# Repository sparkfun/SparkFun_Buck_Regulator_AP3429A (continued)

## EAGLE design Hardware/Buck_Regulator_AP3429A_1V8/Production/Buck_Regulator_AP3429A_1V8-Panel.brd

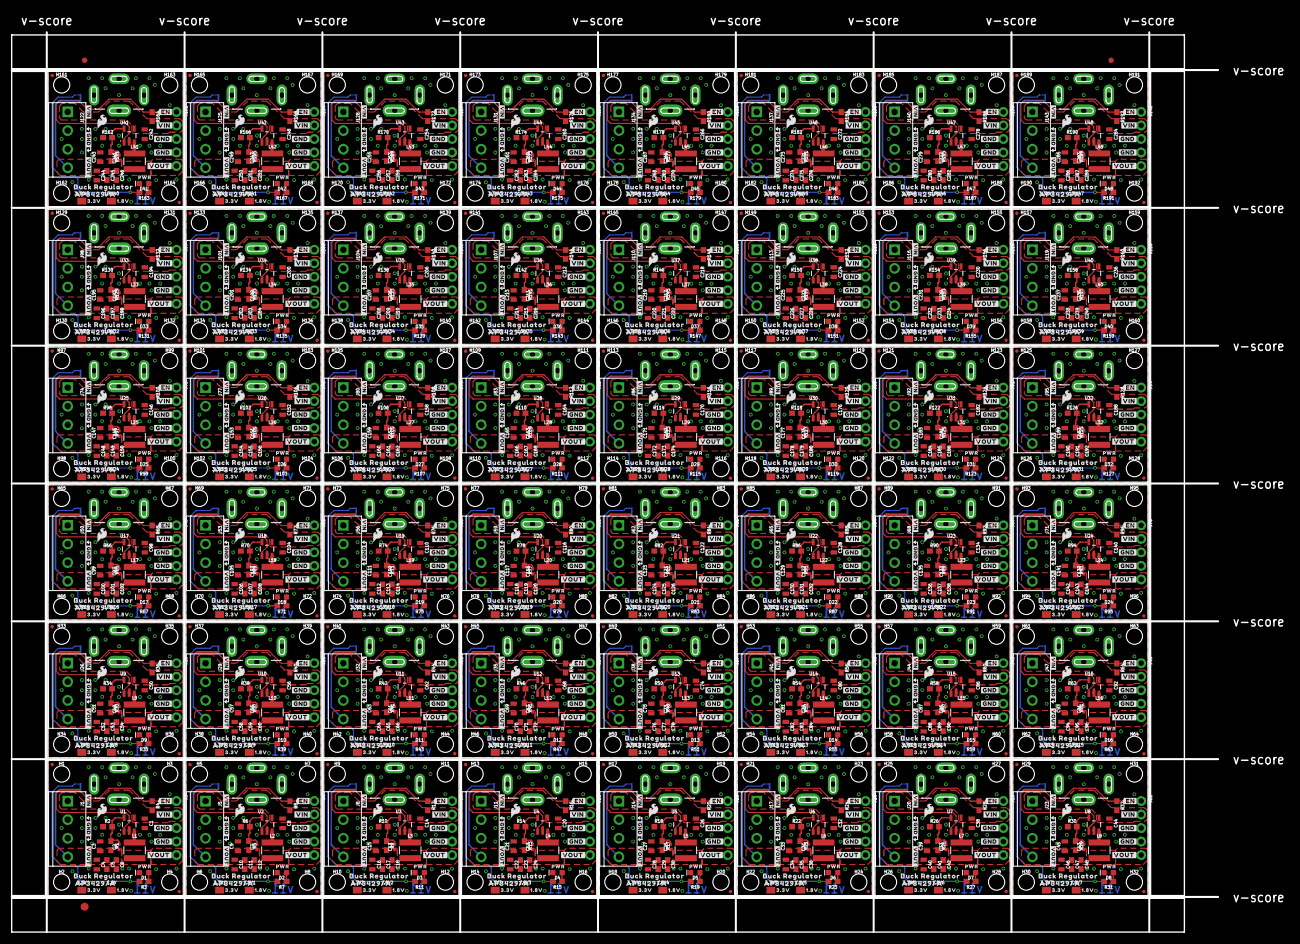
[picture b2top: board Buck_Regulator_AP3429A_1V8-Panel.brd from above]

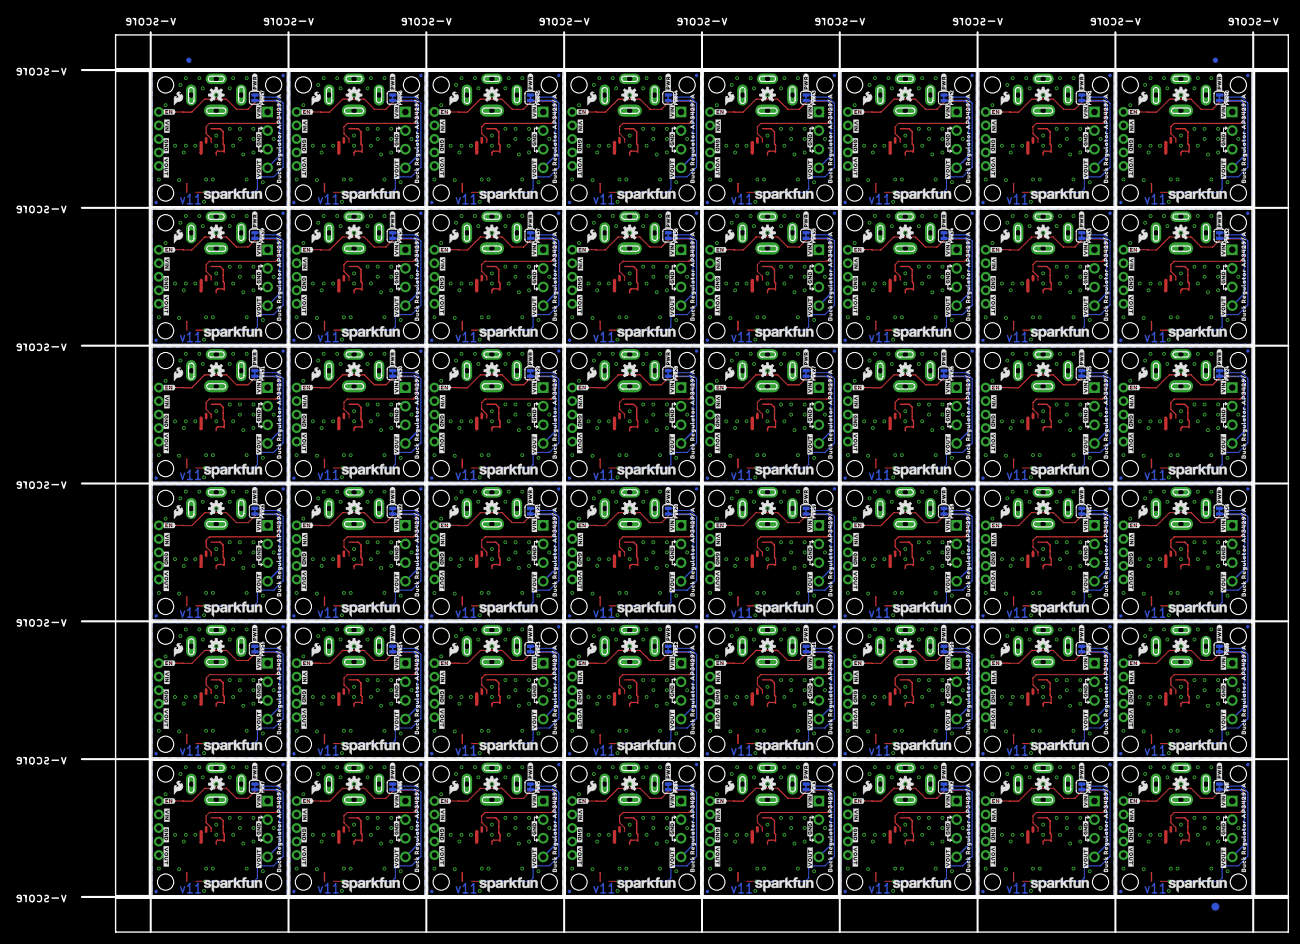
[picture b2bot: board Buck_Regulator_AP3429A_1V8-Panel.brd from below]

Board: 2 copper layers, 226.8 x 169.2 mm, 2550 parts (723 on the bottom side), 384 nets.

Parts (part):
1.8V, 1.8V1, 1.8V2, 1.8V3, 1.8V4, 1.8V5, 1.8V6, 1.8V7, 1.8V8, 1.8V9, 1.8V10, 1.8V11, 1.8V12, 1.8V13, 1.8V14, 1.8V15, 1.8V16, 1.8V17, 1.8V18, 1.8V19, 1.8V20, 1.8V21, 1.8V22, 1.8V23, 1.8V24, 1.8V25, 1.8V26, 1.8V27, 1.8V28, 1.8V29, 1.8V30, 1.8V31, 1.8V32, 1.8V33, 1.8V34, 1.8V35, 1.8V36, 1.8V37, 1.8V38, 1.8V39, 1.8V40, 1.8V41, 1.8V42, 1.8V43, 1.8V44, 1.8V45, 1.8V46, 1.8V47: PROD_ID_PASTE_NO-SILK; PRODUCT_IDENT_PASTE_NO-SILK
3.3V, 3.3V1, 3.3V2, 3.3V3, 3.3V4, 3.3V5, 3.3V6, 3.3V7, 3.3V8, 3.3V9, 3.3V10, 3.3V11, 3.3V12, 3.3V13, 3.3V14, 3.3V15, 3.3V16, 3.3V17, 3.3V18, 3.3V19, 3.3V20, 3.3V21, 3.3V22, 3.3V23, 3.3V24, 3.3V25, 3.3V26, 3.3V27, 3.3V28, 3.3V29, 3.3V30, 3.3V31, 3.3V32, 3.3V33, 3.3V34, 3.3V35, 3.3V36, 3.3V37, 3.3V38, 3.3V39, 3.3V40, 3.3V41, 3.3V42, 3.3V43, 3.3V44, 3.3V45, 3.3V46, 3.3V47: PROD_ID_NO-PASTE_NO_SILK; PRODUCT_IDENT_NO_NO-SILK
C1, C3, C4, C8, C9, C10, C14, C15, C16, C20, C21, C22, C26, C27, C28, C32, C33, C34, C38, C39, C40, C44, C45, C46, C50, C51, C52, C56, C57, C58, C62, C63, C64, C68, C69, C70, C74, C75, C76, C80, C81, C82, C86, C87, C88, C92, C93, C94, C98, C99, C100, C104, C105, C106, C110, C111, C112, C116, C117, C118, C122, C123, C124, C128, C129, C130, C134, C135, C136, C140, C141, C142, C146, C147, C148, C152, C153, C154, C158, C159, C160, C164, C165, C166, C170, C171, C172, C176, C177, C178, C182, C183, C184, C188, C189, C190, C194, C195, C196, C200, C201, C202, C206, C207, C208, C212, C213, C214, C218, C219, C220, C224, C225, C226, C230, C231, C232, C236, C237, C238, C242, C243, C244, C248, C249, C250, C254, C255, C256, C260, C261, C262, C266, C267, C268, C272, C273, C274, C278, C279, C280, C284, C285, C286: 22uF; 0805
C2, C7, C13, C19, C25, C31, C37, C43, C49, C55, C61, C67, C73, C79, C85, C91, C97, C103, C109, C115, C121, C127, C133, C139, C145, C151, C157, C163, C169, C175, C181, C187, C193, C199, C205, C211, C217, C223, C229, C235, C241, C247, C253, C259, C265, C271, C277, C283: 22pF; 0402-TIGHT
C5, C11, C17, C23, C29, C35, C41, C47, C53, C59, C65, C71, C77, C83, C89, C95, C101, C107, C113, C119, C125, C131, C137, C143, C149, C155, C161, C167, C173, C179, C185, C191, C197, C203, C209, C215, C221, C227, C233, C239, C245, C251, C257, C263, C269, C275, C281, C287: 0.1uF; 0603
C6, C12, C18, C24, C30, C36, C42, C48, C54, C60, C66, C72, C78, C84, C90, C96, C102, C108, C114, C120, C126, C132, C138, C144, C150, C156, C162, C168, C174, C180, C186, C192, C198, C204, C210, C216, C222, C228, C234, C240, C246, C252, C258, C264, C270, C276, C282, C288: 1.0uF; 0603
D1, D2, D3, D4, D5, D6, D7, D8, D9, D10, D11, D12, D13, D14, D15, D16, D17, D18, D19, D20, D21, D22, D23, D24, D25, D26, D27, D28, D29, D30, D31, D32, D33, D34, D35, D36, D37, D38, D39, D40, D41, D42, D43, D44, D45, D46, D47, D48: RED; LED-0603
E$1, E$2, E$3, E$4: FIDUCIAL-1X2
E$5, E$6: FIDUCIAL-1.5X3
FD1, FD2, FD3, FD4, FD5, FD6, FD7, FD8, FD9, FD10, FD11, FD12, FD13, FD14, FD15, FD16, FD17, FD18, FD19, FD20, FD21, FD22, FD23, FD24, FD25, FD26, FD27, FD28, FD29, FD30, FD31, FD32, FD33, FD34, FD35, FD36, FD37, FD38, FD39, FD40, FD41, FD42, FD43, FD44, FD45, FD46, FD47, FD48, FD49, FD50, FD51, FD52, FD53, FD54, FD55, FD56, FD57, FD58, FD59, FD60, FD61, FD62, FD63, FD64, FD65, FD66, FD67, FD68, FD69, FD70, FD71, FD72, FD73, FD74, FD75, FD76, FD77, FD78, FD79, FD80, FD81, FD82, FD83, FD84, FD85, FD86, FD87, FD88, FD89, FD90, FD91, FD92, FD93, FD94, FD95, FD96, FD97, FD98, FD99, FD100, FD101, FD102, FD103, FD104, FD105, FD106, FD107, FD108, FD109, FD110, FD111, FD112, FD113, FD114, FD115, FD116, FD117, FD118, FD119, FD120, FD121, FD122, FD123, FD124, FD125, FD126, FD127, FD128, FD129, FD130, FD131, FD132, FD133, FD134, FD135, FD136, FD137, FD138, FD139, FD140, FD141, FD142, FD143, FD144, FD145, FD146, FD147, FD148, FD149, FD150, FD151, FD152, FD153, FD154, FD155, FD156, FD157, FD158, FD159, FD160, FD161, FD162, FD163, FD164, FD165, FD166, FD167, FD168, FD169, FD170, FD171, FD172, FD173, FD174, FD175, FD176, FD177, FD178, FD179, FD180, FD181, FD182, FD183, FD184, FD185, FD186, FD187, FD188, FD189, FD190, FD191, FD192: FIDUCIALUFIDUCIAL; FIDUCIAL-MICRO
H1, H2, H3, H4, H5, H6, H7, H8, H9, H10, H11, H12, H13, H14, H15, H16, H17, H18, H19, H20, H21, H22, H23, H24, H25, H26, H27, H28, H29, H30, H31, H32, H33, H34, H35, H36, H37, H38, H39, H40, H41, H42, H43, H44, H45, H46, H47, H48, H49, H50, H51, H52, H53, H54, H55, H56, H57, H58, H59, H60, H61, H62, H63, H64, H65, H66, H67, H68, H69, H70, H71, H72, H73, H74, H75, H76, H77, H78, H79, H80, H81, H82, H83, H84, H85, H86, H87, H88, H89, H90, H91, H92, H93, H94, H95, H96, H97, H98, H99, H100, H101, H102, H103, H104, H105, H106, H107, H108, H109, H110, H111, H112, H113, H114, H115, H116, H117, H118, H119, H120, H121, H122, H123, H124, H125, H126, H127, H128, H129, H130, H131, H132, H133, H134, H135, H136, H137, H138, H139, H140, H141, H142, H143, H144, H145, H146, H147, H148, H149, H150, H151, H152, H153, H154, H155, H156, H157, H158, H159, H160, H161, H162, H163, H164, H165, H166, H167, H168, H169, H170, H171, H172, H173, H174, H175, H176, H177, H178, H179, H180, H181, H182, H183, H184, H185, H186, H187, H188, H189, H190, H191, H192: STAND-OFFTIGHT; STAND-OFF-TIGHT
J1, J5, J8, J11, J14, J17, J20, J23, J26, J29, J32, J35, J38, J41, J44, J47, J50, J53, J56, J59, J62, J65, J68, J71, J74, J77, J80, J83, J86, J89, J92, J95, J98, J101, J104, J107, J110, J113, J116, J119, J122, J125, J128, J131, J134, J137, J140, J143: Screw Terminal; SCREWTERMINAL-3.5MM-4
J2, J6, J9, J12, J15, J18, J21, J24, J27, J30, J33, J36, J39, J42, J45, J48, J51, J54, J57, J60, J63, J66, J69, J72, J75, J78, J81, J84, J87, J90, J93, J96, J99, J102, J105, J108, J111, J114, J117, J120, J123, J126, J129, J132, J135, J138, J141, J144: POWER_JACKPOWER_JACK_SLOT_COMBO; POWER_JACK_PTH_SLOT_BOTH
J3, J4, J7, J10, J13, J16, J19, J22, J25, J28, J31, J34, J37, J40, J43, J46, J49, J52, J55, J58, J61, J64, J67, J70, J73, J76, J79, J82, J85, J88, J91, J94, J97, J100, J103, J106, J109, J112, J115, J118, J121, J124, J127, J130, J133, J136, J139, J142: Breakout Headers; 1X05_NO_SILK
L1, L2, L3, L4, L5, L6, L7, L8, L9, L10, L11, L12, L13, L14, L15, L16, L17, L18, L19, L20, L21, L22, L23, L24, L25, L26, L27, L28, L29, L30, L31, L32, L33, L34, L35, L36, L37, L38, L39, L40, L41, L42, L43, L44, L45, L46, L47, L48: 2.2μH; INDUCTOR_4X4MM
LOGO1, LOGO4, LOGO7, LOGO10, LOGO13, LOGO16, LOGO19, LOGO22, LOGO25, LOGO28, LOGO31, LOGO34, LOGO37, LOGO40, LOGO43, LOGO46, LOGO49, LOGO52, LOGO55, LOGO58, LOGO61, LOGO64, LOGO67, LOGO70, LOGO73, LOGO76, LOGO79, LOGO82, LOGO85, LOGO88, LOGO91, LOGO94, LOGO97, LOGO100, LOGO103, LOGO106, LOGO109, LOGO112, LOGO115, LOGO118, LOGO121, LOGO124, LOGO127, LOGO130, LOGO133, LOGO136, LOGO139, LOGO142: OSHW-LOGOS; OSHW-LOGO-S
LOGO2, LOGO6, LOGO9, LOGO12, LOGO15, LOGO18, LOGO21, LOGO24, LOGO27, LOGO30, LOGO33, LOGO36, LOGO39, LOGO42, LOGO45, LOGO48, LOGO51, LOGO54, LOGO57, LOGO60, LOGO63, LOGO66, LOGO69, LOGO72, LOGO75, LOGO78, LOGO81, LOGO84, LOGO87, LOGO90, LOGO93, LOGO96, LOGO99, LOGO102, LOGO105, LOGO108, LOGO111, LOGO114, LOGO117, LOGO120, LOGO123, LOGO126, LOGO129, LOGO132, LOGO135, LOGO138, LOGO141, LOGO144: SFE_LOGO_NAME.1_INCH; SFE_LOGO_NAME_.1
LOGO3, LOGO5, LOGO8, LOGO11, LOGO14, LOGO17, LOGO20, LOGO23, LOGO26, LOGO29, LOGO32, LOGO35, LOGO38, LOGO41, LOGO44, LOGO47, LOGO50, LOGO53, LOGO56, LOGO59, LOGO62, LOGO65, LOGO68, LOGO71, LOGO74, LOGO77, LOGO80, LOGO83, LOGO86, LOGO89, LOGO92, LOGO95, LOGO98, LOGO101, LOGO104, LOGO107, LOGO110, LOGO113, LOGO116, LOGO119, LOGO122, LOGO125, LOGO128, LOGO131, LOGO134, LOGO137, LOGO140, LOGO143: SFE_LOGO_FLAME.1_INCH; SFE_LOGO_FLAME_.1
PWR, PWR1, PWR2, PWR3, PWR4, PWR5, PWR6, PWR7, PWR8, PWR9, PWR10, PWR11, PWR12, PWR13, PWR14, PWR15, PWR16, PWR17, PWR18, PWR19, PWR20, PWR21, PWR22, PWR23, PWR24, PWR25, PWR26, PWR27, PWR28, PWR29, PWR30, PWR31, PWR32, PWR33, PWR34, PWR35, PWR36, PWR37, PWR38, PWR39, PWR40, PWR41, PWR42, PWR43, PWR44, PWR45, PWR46, PWR47: JUMPER-SMT_2_NC_TRACE_SILK; SMT-JUMPER_2_NC_TRACE_SILK
R1, R5, R9, R13, R17, R21, R25, R29, R33, R37, R41, R45, R49, R53, R57, R61, R65, R69, R73, R77, R81, R85, R89, R93, R97, R101, R105, R109, R113, R117, R121, R125, R129, R133, R137, R141, R145, R149, R153, R157, R161, R165, R169, R173, R177, R181, R185, R189: 300k; 0603
R2, R6, R10, R14, R18, R22, R26, R30, R34, R38, R42, R46, R50, R54, R58, R62, R66, R70, R74, R78, R82, R86, R90, R94, R98, R102, R106, R110, R114, R118, R122, R126, R130, R134, R138, R142, R146, R150, R154, R158, R162, R166, R170, R174, R178, R182, R186, R190: 150k; 0603
R3, R7, R11, R15, R19, R23, R27, R31, R35, R39, R43, R47, R51, R55, R59, R63, R67, R71, R75, R79, R83, R87, R91, R95, R99, R103, R107, R111, R115, R119, R123, R127, R131, R135, R139, R143, R147, R151, R155, R159, R163, R167, R171, R175, R179, R183, R187, R191: 100; 0603
R4, R8, R12, R16, R20, R24, R28, R32, R36, R40, R44, R48, R52, R56, R60, R64, R68, R72, R76, R80, R84, R88, R92, R96, R100, R104, R108, R112, R116, R120, R124, R128, R132, R136, R140, R144, R148, R152, R156, R160, R164, R168, R172, R176, R180, R184, R188, R192: 100k; 0603
U1, U2, U3, U4, U5, U6, U7, U8, U9, U10, U11, U12, U13, U14, U15, U16, U17, U18, U19, U20, U21, U22, U23, U24, U25, U26, U27, U28, U29, U30, U31, U32, U33, U34, U35, U36, U37, U38, U39, U40, U41, U42, U43, U44, U45, U46, U47, U48: AP3429/A; SOT23-5
U$1, U$17, U$47, U$70, U$93, U$116, U$139, U$162, U$185, U$208, U$231, U$254, U$277, U$300, U$323, U$346, U$369, U$392, U$415, U$438, U$461, U$484, U$507, U$530, U$553, U$576, U$599, U$622, U$645, U$668, U$691, U$714, U$737, U$760, U$783, U$806, U$829, U$852, U$875, U$898, U$921, U$944, U$967, U$990, U$1013, U$1036, U$1059, U$1082: SFE_LOGO_FLAME_.1
U$2, U$18, U$48, U$71, U$94, U$117, U$140, U$163, U$186, U$209, U$232, U$255, U$278, U$301, U$324, U$347, U$370, U$393, U$416, U$439, U$462, U$485, U$508, U$531, U$554, U$577, U$600, U$623, U$646, U$669, U$692, U$715, U$738, U$761, U$784, U$807, U$830, U$853, U$876, U$899, U$922, U$945, U$968, U$991, U$1014, U$1037, U$1060, U$1083: BUCK_REGULATOR24
U$3, U$26, U$49, U$72, U$95, U$118, U$141, U$164, U$187, U$210, U$233, U$256, U$279, U$302, U$325, U$348, U$371, U$394, U$417, U$440, U$463, U$486, U$509, U$532, U$555, U$578, U$601, U$624, U$647, U$670, U$693, U$716, U$739, U$762, U$785, U$808, U$831, U$854, U$877, U$900, U$923, U$946, U$969, U$992, U$1015, U$1038, U$1061, U$1084: AP3429#A25
U$4, U$27, U$50, U$73, U$96, U$119, U$142, U$165, U$188, U$211, U$234, U$257, U$280, U$303, U$326, U$349, U$372, U$395, U$418, U$441, U$464, U$487, U$510, U$533, U$556, U$579, U$602, U$625, U$648, U$671, U$694, U$717, U$740, U$763, U$786, U$809, U$832, U$855, U$878, U$901, U$924, U$947, U$970, U$993, U$1016, U$1039, U$1062, U$1085: #VOUT#3431
U$5, U$6, U$28, U$29, U$51, U$52, U$74, U$75, U$97, U$98, U$120, U$121, U$143, U$144, U$166, U$167, U$189, U$190, U$212, U$213, U$235, U$236, U$258, U$259, U$281, U$282, U$304, U$305, U$327, U$328, U$350, U$351, U$373, U$374, U$396, U$397, U$419, U$420, U$442, U$443, U$465, U$466, U$488, U$489, U$511, U$512, U$534, U$535, U$557, U$558, U$580, U$581, U$603, U$604, U$626, U$627, U$649, U$650, U$672, U$673, U$695, U$696, U$718, U$719, U$741, U$742, U$764, U$765, U$787, U$788, U$810, U$811, U$833, U$834, U$856, U$857, U$879, U$880, U$902, U$903, U$925, U$926, U$948, U$949, U$971, U$972, U$994, U$995, U$1017, U$1018, U$1040, U$1041, U$1063, U$1064, U$1086, U$1087: #GND#3432
U$7, U$30, U$53, U$76, U$99, U$122, U$145, U$168, U$191, U$214, U$237, U$260, U$283, U$306, U$329, U$352, U$375, U$398, U$421, U$444, U$467, U$490, U$513, U$536, U$559, U$582, U$605, U$628, U$651, U$674, U$697, U$720, U$743, U$766, U$789, U$812, U$835, U$858, U$881, U$904, U$927, U$950, U$973, U$996, U$1019, U$1042, U$1065, U$1088: #VIN#3433
U$8, U$10, U$39, U$42, U$62, U$65, U$85, U$88, U$108, U$111, U$131, U$134, U$154, U$157, U$177, U$180, U$200, U$203, U$223, U$226, U$246, U$249, U$269, U$272, U$292, U$295, U$315, U$318, U$338, U$341, U$361, U$364, U$384, U$387, U$407, U$410, U$430, U$433, U$453, U$456, U$476, U$479, U$499, U$502, U$522, U$525, U$545, U$548, U$568, U$571, U$591, U$594, U$614, U$617, U$637, U$640, U$660, U$663, U$683, U$686, U$706, U$709, U$729, U$732, U$752, U$755, U$775, U$778, U$798, U$801, U$821, U$824, U$844, U$847, U$867, U$870, U$890, U$893, U$913, U$916, U$936, U$939, U$959, U$962, U$982, U$985, U$1005, U$1008, U$1028, U$1031, U$1051, U$1054, U$1074, U$1077, U$1097, U$1100: #GND#3446
U$9, U$15, U$38, U$44, U$61, U$67, U$84, U$90, U$107, U$113, U$130, U$136, U$153, U$159, U$176, U$182, U$199, U$205, U$222, U$228, U$245, U$251, U$268, U$274, U$291, U$297, U$314, U$320, U$337, U$343, U$360, U$366, U$383, U$389, U$406, U$412, U$429, U$435, U$452, U$458, U$475, U$481, U$498, U$504, U$521, U$527, U$544, U$550, U$567, U$573, U$590, U$596, U$613, U$619, U$636, U$642, U$659, U$665, U$682, U$688, U$705, U$711, U$728, U$734, U$751, U$757, U$774, U$780, U$797, U$803, U$820, U$826, U$843, U$849, U$866, U$872, U$889, U$895, U$912, U$918, U$935, U$941, U$958, U$964, U$981, U$987, U$1004, U$1010, U$1027, U$1033, U$1050, U$1056, U$1073, U$1079, U$1096, U$1102: #VIN#3445
U$11, U$13, U$40, U$43, U$63, U$66, U$86, U$89, U$109, U$112, U$132, U$135, U$155, U$158, U$178, U$181, U$201, U$204, U$224, U$227, U$247, U$250, U$270, U$273, U$293, U$296, U$316, U$319, U$339, U$342, U$362, U$365, U$385, U$388, U$408, U$411, U$431, U$434, U$454, U$457, U$477, U$480, U$500, U$503, U$523, U$526, U$546, U$549, U$569, U$572, U$592, U$595, U$615, U$618, U$638, U$641, U$661, U$664, U$684, U$687, U$707, U$710, U$730, U$733, U$753, U$756, U$776, U$779, U$799, U$802, U$822, U$825, U$845, U$848, U$868, U$871, U$891, U$894, U$914, U$917, U$937, U$940, U$960, U$963, U$983, U$986, U$1006, U$1009, U$1029, U$1032, U$1052, U$1055, U$1075, U$1078, U$1098, U$1101: #VOUT#3447
U$12, U$41, U$64, U$87, U$110, U$133, U$156, U$179, U$202, U$225, U$248, U$271, U$294, U$317, U$340, U$363, U$386, U$409, U$432, U$455, U$478, U$501, U$524, U$547, U$570, U$593, U$616, U$639, U$662, U$685, U$708, U$731, U$754, U$777, U$800, U$823, U$846, U$869, U$892, U$915, U$938, U$961, U$984, U$1007, U$1030, U$1053, U$1076, U$1099: #EN#3448
U$14, U$45, U$68, U$91, U$114, U$137, U$160, U$183, U$206, U$229, U$252, U$275, U$298, U$321, U$344, U$367, U$390, U$413, U$436, U$459, U$482, U$505, U$528, U$551, U$574, U$597, U$620, U$643, U$666, U$689, U$712, U$735, U$758, U$781, U$804, U$827, U$850, U$873, U$896, U$919, U$942, U$965, U$988, U$1011, U$1034, U$1057, U$1080, U$1103: #PWR#3451
U$16, U$46, U$69, U$92, U$115, U$138, U$161, U$184, U$207, U$230, U$253, U$276, U$299, U$322, U$345, U$368, U$391, U$414, U$437, U$460, U$483, U$506, U$529, U$552, U$575, U$598, U$621, U$644, U$667, U$690, U$713, U$736, U$759, U$782, U$805, U$828, U$851, U$874, U$897, U$920, U$943, U$966, U$989, U$1012, U$1035, U$1058, U$1081, U$1104: BUCK_REGULATOR_AP3429#A3453
U$19, U$35, U$58, U$81, U$104, U$127, U$150, U$173, U$196, U$219, U$242, U$265, U$288, U$311, U$334, U$357, U$380, U$403, U$426, U$449, U$472, U$495, U$518, U$541, U$564, U$587, U$610, U$633, U$656, U$679, U$702, U$725, U$748, U$771, U$794, U$817, U$840, U$863, U$886, U$909, U$932, U$955, U$978, U$1001, U$1024, U$1047, U$1070, U$1093: 1#8V3441
U$20, U$36, U$59, U$82, U$105, U$128, U$151, U$174, U$197, U$220, U$243, U$266, U$289, U$312, U$335, U$358, U$381, U$404, U$427, U$450, U$473, U$496, U$519, U$542, U$565, U$588, U$611, U$634, U$657, U$680, U$703, U$726, U$749, U$772, U$795, U$818, U$841, U$864, U$887, U$910, U$933, U$956, U$979, U$1002, U$1025, U$1048, U$1071, U$1094: PWR3441
U$21, U$31, U$54, U$77, U$100, U$123, U$146, U$169, U$192, U$215, U$238, U$261, U$284, U$307, U$330, U$353, U$376, U$399, U$422, U$445, U$468, U$491, U$514, U$537, U$560, U$583, U$606, U$629, U$652, U$675, U$698, U$721, U$744, U$767, U$790, U$813, U$836, U$859, U$882, U$905, U$928, U$951, U$974, U$997, U$1020, U$1043, U$1066, U$1089: #VOUT#3437
U$22, U$32, U$55, U$78, U$101, U$124, U$147, U$170, U$193, U$216, U$239, U$262, U$285, U$308, U$331, U$354, U$377, U$400, U$423, U$446, U$469, U$492, U$515, U$538, U$561, U$584, U$607, U$630, U$653, U$676, U$699, U$722, U$745, U$768, U$791, U$814, U$837, U$860, U$883, U$906, U$929, U$952, U$975, U$998, U$1021, U$1044, U$1067, U$1090: #VIN#3438
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
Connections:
EN: J3.1, R4.1, U1.1
EN1: J4.1, R8.1, U2.1
EN2: J7.1, R12.1, U3.1
EN3: J10.1, R16.1, U4.1
EN4: J13.1, R20.1, U5.1
EN5: J16.1, R24.1, U6.1
EN6: J19.1, R28.1, U7.1
EN7: J22.1, R32.1, U8.1
EN8: J25.1, R36.1, U9.1
EN9: J28.1, R40.1, U10.1
EN10: J31.1, R44.1, U11.1
EN11: J34.1, R48.1, U12.1
EN12: J37.1, R52.1, U13.1
EN13: J40.1, R56.1, U14.1
EN14: J43.1, R60.1, U15.1
EN15: J46.1, R64.1, U16.1
EN16: J49.1, R68.1, U17.1
EN17: J52.1, R72.1, U18.1
EN18: J55.1, R76.1, U19.1
EN19: J58.1, R80.1, U20.1
EN20: J61.1, R84.1, U21.1
EN21: J64.1, R88.1, U22.1
EN22: J67.1, R92.1, U23.1
EN23: J70.1, R96.1, U24.1
EN24: J73.1, R100.1, U25.1
EN25: J76.1, R104.1, U26.1
EN26: J79.1, R108.1, U27.1
EN27: J82.1, R112.1, U28.1
EN28: J85.1, R116.1, U29.1
EN29: J88.1, R120.1, U30.1
EN30: J91.1, R124.1, U31.1
EN31: J94.1, R128.1, U32.1
EN32: J97.1, R132.1, U33.1
EN33: J100.1, R136.1, U34.1
EN34: J103.1, R140.1, U35.1
EN35: J106.1, R144.1, U36.1
EN36: J109.1, R148.1, U37.1
EN37: J112.1, R152.1, U38.1
EN38: J115.1, R156.1, U39.1
EN39: J118.1, R160.1, U40.1
EN40: J121.1, R164.1, U41.1
EN41: J124.1, R168.1, U42.1
EN42: J127.1, R172.1, U43.1
EN43: J130.1, R176.1, U44.1
EN44: J133.1, R180.1, U45.1
EN45: J136.1, R184.1, U46.1
EN46: J139.1, R188.1, U47.1
EN47: J142.1, R192.1, U48.1
GND: C1.2, C3.2, C4.2, C5.2, C6.2, D1.C, J1.2, J1.3, J2.GND, J3.3, J3.4, R2.1, U1.2
GND1: C8.2, C9.2, C10.2, C11.2, C12.2, D2.C, J4.3, J4.4, J5.2, J5.3, J6.GND, R6.1, U2.2
GND2: C14.2, C15.2, C16.2, C17.2, C18.2, D3.C, J7.3, J7.4, J8.2, J8.3, J9.GND, R10.1, U3.2
GND3: C20.2, C21.2, C22.2, C23.2, C24.2, D4.C, J10.3, J10.4, J11.2, J11.3, J12.GND, R14.1, U4.2
GND4: C26.2, C27.2, C28.2, C29.2, C30.2, D5.C, J13.3, J13.4, J14.2, J14.3, J15.GND, R18.1, U5.2
GND5: C32.2, C33.2, C34.2, C35.2, C36.2, D6.C, J16.3, J16.4, J17.2, J17.3, J18.GND, R22.1, U6.2
GND6: C38.2, C39.2, C40.2, C41.2, C42.2, D7.C, J19.3, J19.4, J20.2, J20.3, J21.GND, R26.1, U7.2
GND7: C44.2, C45.2, C46.2, C47.2, C48.2, D8.C, J22.3, J22.4, J23.2, J23.3, J24.GND, R30.1, U8.2
GND8: C50.2, C51.2, C52.2, C53.2, C54.2, D9.C, J25.3, J25.4, J26.2, J26.3, J27.GND, R34.1, U9.2
GND9: C56.2, C57.2, C58.2, C59.2, C60.2, D10.C, J28.3, J28.4, J29.2, J29.3, J30.GND, R38.1, U10.2
GND10: C62.2, C63.2, C64.2, C65.2, C66.2, D11.C, J31.3, J31.4, J32.2, J32.3, J33.GND, R42.1, U11.2
GND11: C68.2, C69.2, C70.2, C71.2, C72.2, D12.C, J34.3, J34.4, J35.2, J35.3, J36.GND, R46.1, U12.2
GND12: C74.2, C75.2, C76.2, C77.2, C78.2, D13.C, J37.3, J37.4, J38.2, J38.3, J39.GND, R50.1, U13.2
GND13: C80.2, C81.2, C82.2, C83.2, C84.2, D14.C, J40.3, J40.4, J41.2, J41.3, J42.GND, R54.1, U14.2
GND14: C86.2, C87.2, C88.2, C89.2, C90.2, D15.C, J43.3, J43.4, J44.2, J44.3, J45.GND, R58.1, U15.2
GND15: C92.2, C93.2, C94.2, C95.2, C96.2, D16.C, J46.3, J46.4, J47.2, J47.3, J48.GND, R62.1, U16.2
GND16: C98.2, C99.2, C100.2, C101.2, C102.2, D17.C, J49.3, J49.4, J50.2, J50.3, J51.GND, R66.1, U17.2
GND17: C104.2, C105.2, C106.2, C107.2, C108.2, D18.C, J52.3, J52.4, J53.2, J53.3, J54.GND, R70.1, U18.2
GND18: C110.2, C111.2, C112.2, C113.2, C114.2, D19.C, J55.3, J55.4, J56.2, J56.3, J57.GND, R74.1, U19.2
GND19: C116.2, C117.2, C118.2, C119.2, C120.2, D20.C, J58.3, J58.4, J59.2, J59.3, J60.GND, R78.1, U20.2
GND20: C122.2, C123.2, C124.2, C125.2, C126.2, D21.C, J61.3, J61.4, J62.2, J62.3, J63.GND, R82.1, U21.2
GND21: C128.2, C129.2, C130.2, C131.2, C132.2, D22.C, J64.3, J64.4, J65.2, J65.3, J66.GND, R86.1, U22.2
GND22: C134.2, C135.2, C136.2, C137.2, C138.2, D23.C, J67.3, J67.4, J68.2, J68.3, J69.GND, R90.1, U23.2
GND23: C140.2, C141.2, C142.2, C143.2, C144.2, D24.C, J70.3, J70.4, J71.2, J71.3, J72.GND, R94.1, U24.2
GND24: C146.2, C147.2, C148.2, C149.2, C150.2, D25.C, J73.3, J73.4, J74.2, J74.3, J75.GND, R98.1, U25.2
GND25: C152.2, C153.2, C154.2, C155.2, C156.2, D26.C, J76.3, J76.4, J77.2, J77.3, J78.GND, R102.1, U26.2
GND26: C158.2, C159.2, C160.2, C161.2, C162.2, D27.C, J79.3, J79.4, J80.2, J80.3, J81.GND, R106.1, U27.2
GND27: C164.2, C165.2, C166.2, C167.2, C168.2, D28.C, J82.3, J82.4, J83.2, J83.3, J84.GND, R110.1, U28.2
GND28: C170.2, C171.2, C172.2, C173.2, C174.2, D29.C, J85.3, J85.4, J86.2, J86.3, J87.GND, R114.1, U29.2
GND29: C176.2, C177.2, C178.2, C179.2, C180.2, D30.C, J88.3, J88.4, J89.2, J89.3, J90.GND, R118.1, U30.2
GND30: C182.2, C183.2, C184.2, C185.2, C186.2, D31.C, J91.3, J91.4, J92.2, J92.3, J93.GND, R122.1, U31.2
GND31: C188.2, C189.2, C190.2, C191.2, C192.2, D32.C, J94.3, J94.4, J95.2, J95.3, J96.GND, R126.1, U32.2
GND32: C194.2, C195.2, C196.2, C197.2, C198.2, D33.C, J97.3, J97.4, J98.2, J98.3, J99.GND, R130.1, U33.2
GND33: C200.2, C201.2, C202.2, C203.2, C204.2, D34.C, J100.3, J100.4, J101.2, J101.3, J102.GND, R134.1, U34.2
GND34: C206.2, C207.2, C208.2, C209.2, C210.2, D35.C, J103.3, J103.4, J104.2, J104.3, J105.GND, R138.1, U35.2
GND35: C212.2, C213.2, C214.2, C215.2, C216.2, D36.C, J106.3, J106.4, J107.2, J107.3, J108.GND, R142.1, U36.2
GND36: C218.2, C219.2, C220.2, C221.2, C222.2, D37.C, J109.3, J109.4, J110.2, J110.3, J111.GND, R146.1, U37.2
GND37: C224.2, C225.2, C226.2, C227.2, C228.2, D38.C, J112.3, J112.4, J113.2, J113.3, J114.GND, R150.1, U38.2
GND38: C230.2, C231.2, C232.2, C233.2, C234.2, D39.C, J115.3, J115.4, J116.2, J116.3, J117.GND, R154.1, U39.2
GND39: C236.2, C237.2, C238.2, C239.2, C240.2, D40.C, J118.3, J118.4, J119.2, J119.3, J120.GND, R158.1, U40.2
GND40: C242.2, C243.2, C244.2, C245.2, C246.2, D41.C, J121.3, J121.4, J122.2, J122.3, J123.GND, R162.1, U41.2
GND41: C248.2, C249.2, C250.2, C251.2, C252.2, D42.C, J124.3, J124.4, J125.2, J125.3, J126.GND, R166.1, U42.2
GND42: C254.2, C255.2, C256.2, C257.2, C258.2, D43.C, J127.3, J127.4, J128.2, J128.3, J129.GND, R170.1, U43.2
GND43: C260.2, C261.2, C262.2, C263.2, C264.2, D44.C, J130.3, J130.4, J131.2, J131.3, J132.GND, R174.1, U44.2
GND44: C266.2, C267.2, C268.2, C269.2, C270.2, D45.C, J133.3, J133.4, J134.2, J134.3, J135.GND, R178.1, U45.2
GND45: C272.2, C273.2, C274.2, C275.2, C276.2, D46.C, J136.3, J136.4, J137.2, J137.3, J138.GND, R182.1, U46.2
GND46: C278.2, C279.2, C280.2, C281.2, C282.2, D47.C, J139.3, J139.4, J140.2, J140.3, J141.GND, R186.1, U47.2
GND47: C284.2, C285.2, C286.2, C287.2, C288.2, D48.C, J142.3, J142.4, J143.2, J143.3, J144.GND, R190.1, U48.2
unnamed: L1.P$1, U1.3
unnamed: C2.2, R1.1, R2.2, U1.5
unnamed: PWR.1, R3.2
unnamed: D1.A, R3.1
unnamed: L2.P$1, U2.3
unnamed: C7.2, R5.1, R6.2, U2.5
unnamed: PWR1.1, R7.2
unnamed: D2.A, R7.1
unnamed: L3.P$1, U3.3
unnamed: C13.2, R9.1, R10.2, U3.5
unnamed: PWR2.1, R11.2
unnamed: D3.A, R11.1
unnamed: L4.P$1, U4.3
unnamed: C19.2, R13.1, R14.2, U4.5
unnamed: PWR3.1, R15.2
unnamed: D4.A, R15.1
unnamed: L5.P$1, U5.3
unnamed: C25.2, R17.1, R18.2, U5.5
unnamed: PWR4.1, R19.2
unnamed: D5.A, R19.1
unnamed: L6.P$1, U6.3
unnamed: C31.2, R21.1, R22.2, U6.5
unnamed: PWR5.1, R23.2
unnamed: D6.A, R23.1
unnamed: L7.P$1, U7.3
unnamed: C37.2, R25.1, R26.2, U7.5
unnamed: PWR6.1, R27.2
unnamed: D7.A, R27.1
unnamed: L8.P$1, U8.3
unnamed: C43.2, R29.1, R30.2, U8.5
unnamed: PWR7.1, R31.2
unnamed: D8.A, R31.1
unnamed: L9.P$1, U9.3
unnamed: C49.2, R33.1, R34.2, U9.5
unnamed: PWR8.1, R35.2
unnamed: D9.A, R35.1
unnamed: L10.P$1, U10.3
unnamed: C55.2, R37.1, R38.2, U10.5
unnamed: PWR9.1, R39.2
unnamed: D10.A, R39.1
unnamed: L11.P$1, U11.3
unnamed: C61.2, R41.1, R42.2, U11.5
unnamed: PWR10.1, R43.2
unnamed: D11.A, R43.1
unnamed: L12.P$1, U12.3
unnamed: C67.2, R45.1, R46.2, U12.5
unnamed: PWR11.1, R47.2
unnamed: D12.A, R47.1
unnamed: L13.P$1, U13.3
unnamed: C73.2, R49.1, R50.2, U13.5
unnamed: PWR12.1, R51.2
unnamed: D13.A, R51.1
unnamed: L14.P$1, U14.3
unnamed: C79.2, R53.1, R54.2, U14.5
unnamed: PWR13.1, R55.2
unnamed: D14.A, R55.1
unnamed: L15.P$1, U15.3
unnamed: C85.2, R57.1, R58.2, U15.5
unnamed: PWR14.1, R59.2
unnamed: D15.A, R59.1
unnamed: L16.P$1, U16.3
unnamed: C91.2, R61.1, R62.2, U16.5
unnamed: PWR15.1, R63.2
unnamed: D16.A, R63.1
unnamed: L17.P$1, U17.3
unnamed: C97.2, R65.1, R66.2, U17.5
unnamed: PWR16.1, R67.2
unnamed: D17.A, R67.1
unnamed: L18.P$1, U18.3
unnamed: C103.2, R69.1, R70.2, U18.5
unnamed: PWR17.1, R71.2
unnamed: D18.A, R71.1
unnamed: L19.P$1, U19.3
unnamed: C109.2, R73.1, R74.2, U19.5
unnamed: PWR18.1, R75.2
unnamed: D19.A, R75.1
unnamed: L20.P$1, U20.3
unnamed: C115.2, R77.1, R78.2, U20.5
unnamed: PWR19.1, R79.2
unnamed: D20.A, R79.1
unnamed: L21.P$1, U21.3
unnamed: C121.2, R81.1, R82.2, U21.5
unnamed: PWR20.1, R83.2
unnamed: D21.A, R83.1
unnamed: L22.P$1, U22.3
unnamed: C127.2, R85.1, R86.2, U22.5
unnamed: PWR21.1, R87.2
unnamed: D22.A, R87.1
unnamed: L23.P$1, U23.3
unnamed: C133.2, R89.1, R90.2, U23.5
unnamed: PWR22.1, R91.2
unnamed: D23.A, R91.1
unnamed: L24.P$1, U24.3
unnamed: C139.2, R93.1, R94.2, U24.5
unnamed: PWR23.1, R95.2
unnamed: D24.A, R95.1
unnamed: L25.P$1, U25.3
unnamed: C145.2, R97.1, R98.2, U25.5
unnamed: PWR24.1, R99.2
unnamed: D25.A, R99.1
unnamed: L26.P$1, U26.3
unnamed: C151.2, R101.1, R102.2, U26.5
unnamed: PWR25.1, R103.2
unnamed: D26.A, R103.1
unnamed: L27.P$1, U27.3
unnamed: C157.2, R105.1, R106.2, U27.5
unnamed: PWR26.1, R107.2
unnamed: D27.A, R107.1
unnamed: L28.P$1, U28.3
unnamed: C163.2, R109.1, R110.2, U28.5
unnamed: PWR27.1, R111.2
unnamed: D28.A, R111.1
unnamed: L29.P$1, U29.3
unnamed: C169.2, R113.1, R114.2, U29.5
unnamed: PWR28.1, R115.2
unnamed: D29.A, R115.1
unnamed: L30.P$1, U30.3
unnamed: C175.2, R117.1, R118.2, U30.5
unnamed: PWR29.1, R119.2
unnamed: D30.A, R119.1
unnamed: L31.P$1, U31.3
unnamed: C181.2, R121.1, R122.2, U31.5
unnamed: PWR30.1, R123.2
unnamed: D31.A, R123.1
unnamed: L32.P$1, U32.3
unnamed: C187.2, R125.1, R126.2, U32.5
unnamed: PWR31.1, R127.2
unnamed: D32.A, R127.1
unnamed: L33.P$1, U33.3
unnamed: C193.2, R129.1, R130.2, U33.5
unnamed: PWR32.1, R131.2
unnamed: D33.A, R131.1
unnamed: L34.P$1, U34.3
unnamed: C199.2, R133.1, R134.2, U34.5
unnamed: PWR33.1, R135.2
unnamed: D34.A, R135.1
unnamed: L35.P$1, U35.3
unnamed: C205.2, R137.1, R138.2, U35.5
unnamed: PWR34.1, R139.2
unnamed: D35.A, R139.1
unnamed: L36.P$1, U36.3
unnamed: C211.2, R141.1, R142.2, U36.5
unnamed: PWR35.1, R143.2
unnamed: D36.A, R143.1
unnamed: L37.P$1, U37.3
unnamed: C217.2, R145.1, R146.2, U37.5
unnamed: PWR36.1, R147.2
unnamed: D37.A, R147.1
unnamed: L38.P$1, U38.3
unnamed: C223.2, R149.1, R150.2, U38.5
unnamed: PWR37.1, R151.2
unnamed: D38.A, R151.1
unnamed: L39.P$1, U39.3
unnamed: C229.2, R153.1, R154.2, U39.5
unnamed: PWR38.1, R155.2
unnamed: D39.A, R155.1
unnamed: L40.P$1, U40.3
unnamed: C235.2, R157.1, R158.2, U40.5
unnamed: PWR39.1, R159.2
unnamed: D40.A, R159.1
unnamed: L41.P$1, U41.3
unnamed: C241.2, R161.1, R162.2, U41.5
unnamed: PWR40.1, R163.2
unnamed: D41.A, R163.1
unnamed: L42.P$1, U42.3
unnamed: C247.2, R165.1, R166.2, U42.5
unnamed: PWR41.1, R167.2
unnamed: D42.A, R167.1
unnamed: L43.P$1, U43.3
unnamed: C253.2, R169.1, R170.2, U43.5
unnamed: PWR42.1, R171.2
unnamed: D43.A, R171.1
unnamed: L44.P$1, U44.3
unnamed: C259.2, R173.1, R174.2, U44.5
unnamed: PWR43.1, R175.2
unnamed: D44.A, R175.1
unnamed: L45.P$1, U45.3
unnamed: C265.2, R177.1, R178.2, U45.5
unnamed: PWR44.1, R179.2
unnamed: D45.A, R179.1
unnamed: L46.P$1, U46.3
unnamed: C271.2, R181.1, R182.2, U46.5
unnamed: PWR45.1, R183.2
unnamed: D46.A, R183.1
unnamed: L47.P$1, U47.3
unnamed: C277.2, R185.1, R186.2, U47.5
unnamed: PWR46.1, R187.2
unnamed: D47.A, R187.1
unnamed: L48.P$1, U48.3
unnamed: C283.2, R189.1, R190.2, U48.5
unnamed: PWR47.1, R191.2
unnamed: D48.A, R191.1
VIN: C1.1, J1.1, J2.PWR, J3.2, R4.2, U1.4
VIN1: C8.1, J4.2, J5.1, J6.PWR, R8.2, U2.4
VIN2: C14.1, J7.2, J8.1, J9.PWR, R12.2, U3.4
VIN3: C20.1, J10.2, J11.1, J12.PWR, R16.2, U4.4
VIN4: C26.1, J13.2, J14.1, J15.PWR, R20.2, U5.4
VIN5: C32.1, J16.2, J17.1, J18.PWR, R24.2, U6.4
VIN6: C38.1, J19.2, J20.1, J21.PWR, R28.2, U7.4
VIN7: C44.1, J22.2, J23.1, J24.PWR, R32.2, U8.4
VIN8: C50.1, J25.2, J26.1, J27.PWR, R36.2, U9.4
VIN9: C56.1, J28.2, J29.1, J30.PWR, R40.2, U10.4
VIN10: C62.1, J31.2, J32.1, J33.PWR, R44.2, U11.4
VIN11: C68.1, J34.2, J35.1, J36.PWR, R48.2, U12.4
VIN12: C74.1, J37.2, J38.1, J39.PWR, R52.2, U13.4
VIN13: C80.1, J40.2, J41.1, J42.PWR, R56.2, U14.4
VIN14: C86.1, J43.2, J44.1, J45.PWR, R60.2, U15.4
VIN15: C92.1, J46.2, J47.1, J48.PWR, R64.2, U16.4
VIN16: C98.1, J49.2, J50.1, J51.PWR, R68.2, U17.4
VIN17: C104.1, J52.2, J53.1, J54.PWR, R72.2, U18.4
VIN18: C110.1, J55.2, J56.1, J57.PWR, R76.2, U19.4
VIN19: C116.1, J58.2, J59.1, J60.PWR, R80.2, U20.4
VIN20: C122.1, J61.2, J62.1, J63.PWR, R84.2, U21.4
VIN21: C128.1, J64.2, J65.1, J66.PWR, R88.2, U22.4
VIN22: C134.1, J67.2, J68.1, J69.PWR, R92.2, U23.4
VIN23: C140.1, J70.2, J71.1, J72.PWR, R96.2, U24.4
VIN24: C146.1, J73.2, J74.1, J75.PWR, R100.2, U25.4
VIN25: C152.1, J76.2, J77.1, J78.PWR, R104.2, U26.4
VIN26: C158.1, J79.2, J80.1, J81.PWR, R108.2, U27.4
VIN27: C164.1, J82.2, J83.1, J84.PWR, R112.2, U28.4
VIN28: C170.1, J85.2, J86.1, J87.PWR, R116.2, U29.4
VIN29: C176.1, J88.2, J89.1, J90.PWR, R120.2, U30.4
VIN30: C182.1, J91.2, J92.1, J93.PWR, R124.2, U31.4
VIN31: C188.1, J94.2, J95.1, J96.PWR, R128.2, U32.4
VIN32: C194.1, J97.2, J98.1, J99.PWR, R132.2, U33.4
VIN33: C200.1, J100.2, J101.1, J102.PWR, R136.2, U34.4
VIN34: C206.1, J103.2, J104.1, J105.PWR, R140.2, U35.4
VIN35: C212.1, J106.2, J107.1, J108.PWR, R144.2, U36.4
VIN36: C218.1, J109.2, J110.1, J111.PWR, R148.2, U37.4
VIN37: C224.1, J112.2, J113.1, J114.PWR, R152.2, U38.4
VIN38: C230.1, J115.2, J116.1, J117.PWR, R156.2, U39.4
VIN39: C236.1, J118.2, J119.1, J120.PWR, R160.2, U40.4
VIN40: C242.1, J121.2, J122.1, J123.PWR, R164.2, U41.4
VIN41: C248.1, J124.2, J125.1, J126.PWR, R168.2, U42.4
VIN42: C254.1, J127.2, J128.1, J129.PWR, R172.2, U43.4
VIN43: C260.1, J130.2, J131.1, J132.PWR, R176.2, U44.4
VIN44: C266.1, J133.2, J134.1, J135.PWR, R180.2, U45.4
VIN45: C272.1, J136.2, J137.1, J138.PWR, R184.2, U46.4
VIN46: C278.1, J139.2, J140.1, J141.PWR, R188.2, U47.4
VIN47: C284.1, J142.2, J143.1, J144.PWR, R192.2, U48.4
VOUT: C2.1, C3.1, C4.1, C5.1, C6.1, J1.4, J3.5, L1.P$2, PWR.2, R1.2
VOUT1: C7.1, C9.1, C10.1, C11.1, C12.1, J4.5, J5.4, L2.P$2, PWR1.2, R5.2
VOUT2: C13.1, C15.1, C16.1, C17.1, C18.1, J7.5, J8.4, L3.P$2, PWR2.2, R9.2
VOUT3: C19.1, C21.1, C22.1, C23.1, C24.1, J10.5, J11.4, L4.P$2, PWR3.2, R13.2
VOUT4: C25.1, C27.1, C28.1, C29.1, C30.1, J13.5, J14.4, L5.P$2, PWR4.2, R17.2
VOUT5: C31.1, C33.1, C34.1, C35.1, C36.1, J16.5, J17.4, L6.P$2, PWR5.2, R21.2
VOUT6: C37.1, C39.1, C40.1, C41.1, C42.1, J19.5, J20.4, L7.P$2, PWR6.2, R25.2
VOUT7: C43.1, C45.1, C46.1, C47.1, C48.1, J22.5, J23.4, L8.P$2, PWR7.2, R29.2
VOUT8: C49.1, C51.1, C52.1, C53.1, C54.1, J25.5, J26.4, L9.P$2, PWR8.2, R33.2
VOUT9: C55.1, C57.1, C58.1, C59.1, C60.1, J28.5, J29.4, L10.P$2, PWR9.2, R37.2
VOUT10: C61.1, C63.1, C64.1, C65.1, C66.1, J31.5, J32.4, L11.P$2, PWR10.2, R41.2
VOUT11: C67.1, C69.1, C70.1, C71.1, C72.1, J34.5, J35.4, L12.P$2, PWR11.2, R45.2
VOUT12: C73.1, C75.1, C76.1, C77.1, C78.1, J37.5, J38.4, L13.P$2, PWR12.2, R49.2
VOUT13: C79.1, C81.1, C82.1, C83.1, C84.1, J40.5, J41.4, L14.P$2, PWR13.2, R53.2
VOUT14: C85.1, C87.1, C88.1, C89.1, C90.1, J43.5, J44.4, L15.P$2, PWR14.2, R57.2
VOUT15: C91.1, C93.1, C94.1, C95.1, C96.1, J46.5, J47.4, L16.P$2, PWR15.2, R61.2
VOUT16: C97.1, C99.1, C100.1, C101.1, C102.1, J49.5, J50.4, L17.P$2, PWR16.2, R65.2
VOUT17: C103.1, C105.1, C106.1, C107.1, C108.1, J52.5, J53.4, L18.P$2, PWR17.2, R69.2
VOUT18: C109.1, C111.1, C112.1, C113.1, C114.1, J55.5, J56.4, L19.P$2, PWR18.2, R73.2
VOUT19: C115.1, C117.1, C118.1, C119.1, C120.1, J58.5, J59.4, L20.P$2, PWR19.2, R77.2
VOUT20: C121.1, C123.1, C124.1, C125.1, C126.1, J61.5, J62.4, L21.P$2, PWR20.2, R81.2
VOUT21: C127.1, C129.1, C130.1, C131.1, C132.1, J64.5, J65.4, L22.P$2, PWR21.2, R85.2
VOUT22: C133.1, C135.1, C136.1, C137.1, C138.1, J67.5, J68.4, L23.P$2, PWR22.2, R89.2
VOUT23: C139.1, C141.1, C142.1, C143.1, C144.1, J70.5, J71.4, L24.P$2, PWR23.2, R93.2
VOUT24: C145.1, C147.1, C148.1, C149.1, C150.1, J73.5, J74.4, L25.P$2, PWR24.2, R97.2
VOUT25: C151.1, C153.1, C154.1, C155.1, C156.1, J76.5, J77.4, L26.P$2, PWR25.2, R101.2
VOUT26: C157.1, C159.1, C160.1, C161.1, C162.1, J79.5, J80.4, L27.P$2, PWR26.2, R105.2
VOUT27: C163.1, C165.1, C166.1, C167.1, C168.1, J82.5, J83.4, L28.P$2, PWR27.2, R109.2
VOUT28: C169.1, C171.1, C172.1, C173.1, C174.1, J85.5, J86.4, L29.P$2, PWR28.2, R113.2
VOUT29: C175.1, C177.1, C178.1, C179.1, C180.1, J88.5, J89.4, L30.P$2, PWR29.2, R117.2
VOUT30: C181.1, C183.1, C184.1, C185.1, C186.1, J91.5, J92.4, L31.P$2, PWR30.2, R121.2
VOUT31: C187.1, C189.1, C190.1, C191.1, C192.1, J94.5, J95.4, L32.P$2, PWR31.2, R125.2
VOUT32: C193.1, C195.1, C196.1, C197.1, C198.1, J97.5, J98.4, L33.P$2, PWR32.2, R129.2
VOUT33: C199.1, C201.1, C202.1, C203.1, C204.1, J100.5, J101.4, L34.P$2, PWR33.2, R133.2
VOUT34: C205.1, C207.1, C208.1, C209.1, C210.1, J103.5, J104.4, L35.P$2, PWR34.2, R137.2
VOUT35: C211.1, C213.1, C214.1, C215.1, C216.1, J106.5, J107.4, L36.P$2, PWR35.2, R141.2
VOUT36: C217.1, C219.1, C220.1, C221.1, C222.1, J109.5, J110.4, L37.P$2, PWR36.2, R145.2
VOUT37: C223.1, C225.1, C226.1, C227.1, C228.1, J112.5, J113.4, L38.P$2, PWR37.2, R149.2
VOUT38: C229.1, C231.1, C232.1, C233.1, C234.1, J115.5, J116.4, L39.P$2, PWR38.2, R153.2
VOUT39: C235.1, C237.1, C238.1, C239.1, C240.1, J118.5, J119.4, L40.P$2, PWR39.2, R157.2
VOUT40: C241.1, C243.1, C244.1, C245.1, C246.1, J121.5, J122.4, L41.P$2, PWR40.2, R161.2
VOUT41: C247.1, C249.1, C250.1, C251.1, C252.1, J124.5, J125.4, L42.P$2, PWR41.2, R165.2
VOUT42: C253.1, C255.1, C256.1, C257.1, C258.1, J127.5, J128.4, L43.P$2, PWR42.2, R169.2
VOUT43: C259.1, C261.1, C262.1, C263.1, C264.1, J130.5, J131.4, L44.P$2, PWR43.2, R173.2
VOUT44: C265.1, C267.1, C268.1, C269.1, C270.1, J133.5, J134.4, L45.P$2, PWR44.2, R177.2
VOUT45: C271.1, C273.1, C274.1, C275.1, C276.1, J136.5, J137.4, L46.P$2, PWR45.2, R181.2
VOUT46: C277.1, C279.1, C280.1, C281.1, C282.1, J139.5, J140.4, L47.P$2, PWR46.2, R185.2
VOUT47: C283.1, C285.1, C286.1, C287.1, C288.1, J142.5, J143.4, L48.P$2, PWR47.2, R189.2

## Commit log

2022-12-05 Created schematic, updated README, deleted/moved folders
    Added the schematic to the project, along with starting to add parts, aesthetics, and attributes. Updated the README with project information, and moved around file folders/deleted the unneeded folde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
2022-12-08 Addition of App Note, Updates to Schematic
    Added connectors, power led, and main ic circuit with correctly rated components. The application note was added for the new product that Diodes Inc. sells, but it is the same exact part as the AP342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
2022-12-08 Update Buck_Regulator_AP3429A.sch
    Attributes added for parts missing that information, finished first draft of initial schematic for 1.8V output, added further notation on what to change for 3.3V output instead of the 1.8V output.
2022-12-09 Created Board file and cleaned up schematic
    Added notation jumpers for 3.3V or 1.8V board, created board file and adjusted components to fit onto the board in a 1x1 form factor.
2022-12-14 Updates to project
    Schematic: Changed indicator pads for soldering which version of board, added further notation, updated Power Jack device in local library.
    Layout: Added power polygons and stitching vias to appropriate areas, finished routing, adjusted Power Jack to be double sided now, fixed silkscreen notation, adjusted version number, worked through 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
2022-12-15 v01 Design Review commit
    Small changes were made after running the python checklist. Added more GND vias, added the Power LED silkscreen indicator, updated dimension layer line width, adjusted polygons for better GND pour co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
2022-12-15 heat sink addition - v01 design review
    Changed the SparkFun logo on the backside of the board and separated the name and flame; added an area on the backside for the heatsink to be added; adjusted silkscreen and components on backside acc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
2022-12-16 Updates from design review
    Restructured file folder and project structure to have design files with two different eagle projects within the same github folder; adjusted components on layout for better loop stability; moved ind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
2022-12-16 Updated 3.3V files to be the same as 1.8V
    Changed the 3 resistors (R1, R2, R3) and placed them in the same location as the 1.8V board files.
2022-12-19 Nudge traces for better GND pour connection on BRD
    Moved some traces for a better GND pour on the top layer.
2022-12-19 Added correct measurements
2022-12-19 Further design review changes - v01
    Added selective solder path to Document layer for the terminal block; moved the silkscreen name on the front to not be covered by the mounting hole anymore when a user uses a screw; nudges the LED po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
2022-12-19 Added files for ordering protos
    Ordering proto type boards - added gerbers and .zip file
2023-02-02 Updated files for design review
    Changed the version number on the board file to be V10 instead of V01, then changed the footprint of the power jack on each side of the board to swap the sides of the exposed copper on the groundbrea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
2023-02-02 Changed version number in schematic, adjusted components
    Moved around some silkscreen in order for easier reading on the backside; changed the version number in the schematic to v10
2023-02-02 Added 2 more output capacitors
    Added more output capacitance to match ALC block - there was some ripple detected during testing so adding these should eliminate that. Adjusted the components on the board accordingly then matched t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
2023-02-03 Added panelized files and gerbers
    Panelized the file to match the other buck regulator. Moved the files out of the hardware folders for consistency and easy finding.
2023-02-03 Design Review changes
    Cleaned up 1.8V Hardware folder by deleting unneeded files, adjusted schematic notes for easier reading, deleted extraneous measures, adjusted GND via sizes to be the same size (15mil), adjusted some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
2023-02-06 Adjusted power jack for panelizing
    There was an issue with overhanging silkscreen for the powerjack since the part is usually populated - the part is not populated for this specific part. This was changed from the device all the way t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
2023-02-06 Updated panelized files
    Adjusted via to no longer be in the way of the bStop on the back for the thermal pad on the backside. Included ordering instructions on the brd files for both 1.8V and 3.3V
2023-02-06 Adjusted ordering instructions
    Changed the ordering instructions to further detail the aspects of the board - 2-layer, 1.6mm thickness, 1oz copper
2023-02-06 Deleted unneeded files
    No longer needed these files since they were for ordering individual boards for prototyping
2023-02-07 Updated dimensions
    Moved the thermal pad dimensions to Layer 49 Reference for easier/cleaner reading for the user. This may change, but keeping consistent with the other Buck Regulator.
2023-03-09 V11 Design Update
    Added 100k resistor to pull EN high to VIN for an easier plug and play application.
2023-03-09 V11 Design updates - remove unneeded files
    Removed unneeded file that appeared in the Documentation folder (???)
2023-03-22 Initial docs commit
    Initial commit for hookup guide files
    Move datasheets to appropriate folder
2023-03-22 Backup files
2023-03-22 Placeholder files
    images, eagle files, schematics, dimensions
2023-03-22 Remove excessive icons
2023-03-22 Update mkdocs.yml
    Uncomment plugins
2023-03-22 Update extra.css
    Remove redundant code
2023-04-04 Updated board files
2023-04-04 Fixes/Updates
    General fixes
    Removed grid cards on single images
    Updated the SparkFun primary color
2023-04-04 LiPo Battery Info
    Added information for powering the boards with a batteries
2023-04-04 Update load_test.md
    Added setup image
2023-04-04 Hookup Guide Pics
    Updated pictures for the hardware assembly and load test sections
2023-04-07 Add new images
2023-04-07 Update getting_started.md
    New product images
2023-04-07 Update getting_started.md
    Linked in previous hookup guide
2023-04-07 Update documentation
    Add LiPo battery information
    Added in thermal profiling charts
    Added in quiescent current measurements
2023-04-07 Update mkdocs.yml
    update header link
2023-04-07 Create header.html
    Override header title
2023-04-07 Update README.md
    Update product images
2023-04-13 Update sfe-logo.svg
    Fix icon sizing
2023-04-13 Update resources.md
    Fix link
    Remove product video link (none)
2023-04-13 Update getting_started.md
    Update alt text
2023-04-13 Create mkdocs.yml
    Provide workflow action to publish page
2023-04-14 Update sfe-logo.svg
    fix viewbox
2023-04-14 Update getting_started.md
    Fix wording
2023-04-14 Deployed feae4df with MkDocs version: 1.4.2
2025-01-08 Fix link
2025-01-08 Deployed 0d5a4e9 with MkDocs version: 1.6.1
2025-01-08 Deployed e091aa3 with MkDocs version: 1.6.1
2025-01-09 Deployed 1f3bde4 with MkDocs version: 1.6.1
2025-01-09 Deployed 5707135 with MkDocs version: 1.6.1
2025-01-09 Deployed f829935 with MkDocs version: 1.6.1
2025-01-09 Update workflow
2025-01-09 Remove pdf generator and hard_copy.md
2025-01-09 Update logos and icons
2025-01-09 Deployed ab37b10 with MkDocs version: 1.6.1
2025-01-09 Update styling and build configuration
2025-01-10 Add thumbnail for docs
2025-01-10 Deployed 7897cf1 with MkDocs version: 1.6.1
2025-02-20 Deployed d15a836 with MkDocs version: 1.6.1
2025-02-26 Revert "Update getting_started.md"
    This reverts commit d15a8363d33befd04e9fd3015acbbb8cc960e581.
2025-02-26 Deployed f81aa92 with MkDocs version: 1.6.1
2026-06-03 Deployed 78b32f6 with MkDocs version: 1.6.1
2026-06-03 Replace center tag
    Fix the deprecated HTML `<center>` tag
2026-06-03 Fix MathJax and KaTeX components
2026-06-03 Remove git-authors plug-in
2026-06-03 Deployed acd275c with MkDocs version: 1.6.1
2026-06-03 Deployed a125e89 with MkDocs version: 1.6.1
